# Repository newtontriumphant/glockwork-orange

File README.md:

# _Glockwork Orange_, by zsharpminor

A "Clockwork Orange" is defined as a human being who has had their free will and moral agency mechanically stripped away, turning them into a predictable, unthinking mechanism controlled by outside forces like the state. The human's natural "juicy" state is manifest in the orange, whereas the clockwork represents the unnaturality and cold predictability of the system.

Anyways, enough 1984; hiya! I'm Udo, better known as @zsharpminor or gh/newtontriumphant, and I have a thing for self-playing instruments. In late 2025, I won Honorable Mention at Hack Club x AMD's _Prototype_ flagship hackathon with [FiddleStein](https://github.com/newtontriumphant/Hackclub_Prototype_Fiddlestein), a fully self-playing violin that utilized a SO-101 robot arm and a 10k-step neural network to imitate a real human arm playing violin. FiddleStein was a great concept, but it sounded _mildly bad_, to be polite. Ever since early 2026, I wanted to create another self-playing instrument that would fit in well with FiddleStein, and Glockwork Orange was the logical next step.

## About Glockwork Orange

Glockwork Orange is a fully self-playing chromatic Glockenspiel that relies on solenoids to play ANY midi file payload by adjusting the instrumentation to fit into two voices!

> Sidenote: in the musical percussion and orchestra community, "glock" is used to abbreviate "glockenspiel" and is in no way related to the firearm brand created by Gaston Glock.

Glockwork Orange was designed for [Hack Club Outpost](https://outpost.hackclub.com/) as an X-Tier project, and is [on the list of X-Tier approved projects](https://docs.google.com/document/d/1faTrnYnGDMR5YSOkvKIAk_NsVOftPFZkB7XtJXA-l8c/edit?tab=t.0) sent out by [@CAN](https://hackclub.slack.com/archives/C0B519PGU22/p1781193322652829?thread_ts=1781016229.290339&cid=C0B519PGU22).

Anyways, enough yapping. A picture plays more than a thousand notes, or however the saying goes. Feast your eyes on the final assembled mockup of Glockwork Orange below.

---

At this point, you're probably asking: **how does this lie-detector-looking-thing work?!&**

Well, it's quite simple.

1. The Arduino sends a logic signal to the PCB being striked.
2. The power supply pushes out 15V and routes it into the PCB chain.
3. The respective PCB converts that signal to the current and voltage required to operate the solenoids.
4. The MOSFET briefly powers the solenoid and, by extension, the LED.
5. The solenoid strikes the key and immediately retracts.
6. Repeat (but don't rinse. handwashing is very bad when it comes to PCBs)!

## The PCB

Glockwork Orange's PCB uses a clever arrangement of transistors, resistors, capacitors, and a MOSFET to power the white JST connectors and their respective fading red LEDs each time the individual MOSFET is triggered.

Oh? What do I hear? You're wondering how this monstrosity was wired? If you have any experience doing ground planes on PCBs, I'd recommend you avert your eyes.

I've also included an image of the PCB's schematic:

The way this schematic works is by dividing the three inputs from the Arduino into segments, which each result in one JST connector and LED being powered at one time.

## The CAD

The way this project works is that it relies on the individual components being screwed down into a plywood project panel with M2 screws. That's why there's M2 screws on EVERY SINGLE COMPONENT in my CAD folder. 

For more information, including images and in-progress screenshots of every single CAD part, refer to [JOURNAL.md](JOURNAL.md). I won't entirely leave you hanging, though. Here's a side-view:

The blue parts are the solenoid holders I designed, and they slot onto the red holder bar that I also designed. The grey parts inside the blue holders refer to the actual solenoids.

## Wiring Diagram

Please excuse ~~my dear aunt sally~~ the sloppy wiring, this is only supposed to be *representative* of the final wiring!

```
+15V --> Red
Shared GND --> Black
Solenoid +/- --> Green
Arduino Signal --> Blue
```

## Firmware

The Glockwork Orange firmware consists of two files: `glockwork_orange.ino`, which runs on the Arduino Mega 2560 and maps all 25 chromatic keys (G2–A4, MIDI 43–69) to digital pins 22–46 driving the IRLZ44N MOSFET gate lines, and `glockwork_host.py`, a Python/Tkinter desktop GUI that parses any MIDI file, re-voices it into two chromatic voices within the glockenspiel's range via octave-shifting, and streams precisely-timed strike commands over USB serial at 115200 baud. The Arduino firmware uses a non-blocking 32-slot ring buffer to schedule and execute 35ms solenoid pulses without any delay() calls, which means the timing is, dare I say so myself, quite accurate across simultaneous voices. The host communicates via a simple ASCII protocol (S to start, N{ms},{note} to schedule a strike, X to stop), making it straightforward to extend or replace the Python frontend with any serial-capable environment.

## The Why And The How

Why did I make Glockwork Orange? Well, this one's pretty simple. I always wanted to make a successor to FiddleStein, one that could permanently work and be mounted in place with actual PCBs rather than precarious wiring and hot glue. (Also, using it to get into Outpost was a pretty fun motivation!)

How did I make Glockwork Orange? The entire process is in [JOURNAL.md](JOURNAL.md). Go read it. No, seriously. A lot of research went into this project, and it's a culmination of thoughts and solenoids. TL;DR, the answer is Patience (and a lack thereof).

## Directory

```
.
├── Assets/ <-- Some of the most important images found in this README
├── CAD/ <-- All CAD source files, as well as a .f3z Archive
├── Firmware/ <-- Simple firmware for the Arduino
├── PCB/ <-- KiCad source files of the PCB, .STEP export of PCB
├── Production/ <-- Gerber files and zipped Gerber files
├── BOM.csv <-- All components required to build this monstrosity
├── JOURNAL.md <-- Detailed explanation and tracking of hours
└── README.md <-- This file!
```

## Mini BOM

**NOTE**: The full BOM is located at [BOM.csv](BOM.csv). PLEASE READ IT. THIS IS ONLY A BREAKDOWN.

**CART SCREENSHOTS** can be found in the [Assets/Cart-Screenshots](Assets/Cart-Screenshots/Digikey_Cart_Final.png) folder. PII has been redacted. If the originals are required, DM @zsharpminor on the Hack Club Slack.

| Item | Total | Link |
| :--- | ---: | :---: |
| DigiKey Components | $480.00 | [↗](BOM.csv) |
| Amazon Components | $122.00 | [↗](BOM.csv) |
| Plywood from THD | $15.00 | [↗](BOM.csv) |
| JLCPCB PCB x 10 | $15.00 | [↗](BOM.csv) |
| Arduino and PSU | **OWNED** | - |
| | **$632.00** | |

## Disclosure of AI Usage

No Artificial Intelligence was used in creating the PCB, Schematic, any of the CAD, or README / JOURNAL.

AI was solely used to automate placing links into the BOM (~10% of BOM tracked hours), and for minor assistance with the code (see bottom of [JOURNAL.md](JOURNAL.md) for additional information), and for creating a custom footprint for an obsolete capacitor.

## License

GNU General Public License (GPL)

---

Thanks for reading down all this way! If you have any questions, please reach out to me via the Hack Club Slack @zsharpminor

Made with ♡ by zsharpminor

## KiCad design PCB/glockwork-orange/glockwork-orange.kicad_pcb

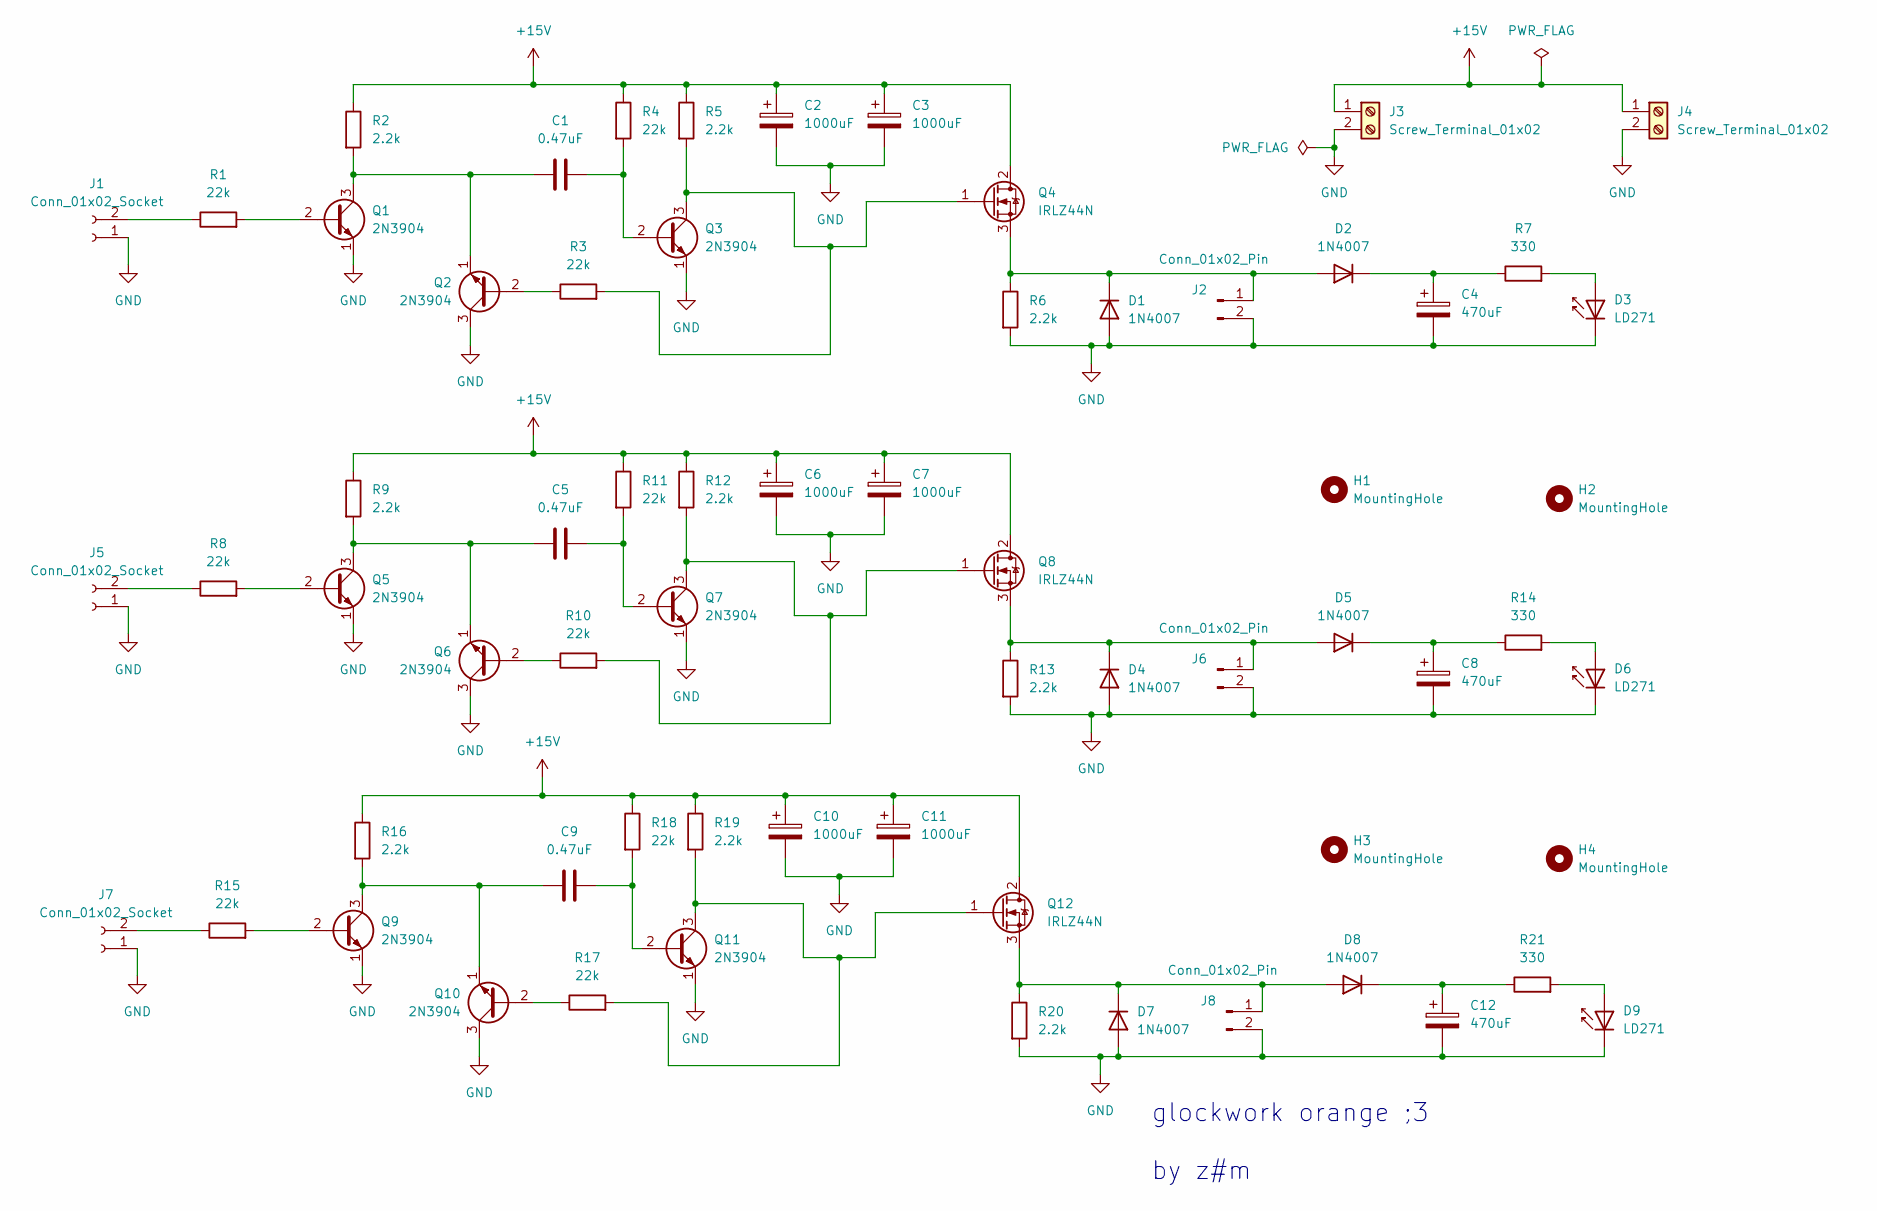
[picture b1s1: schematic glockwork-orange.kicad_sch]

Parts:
C1, C5, C9: 0.47uF; CAPRR750W80L1750T580H1400
C2, C3, C6, C7, C10, C11: 1000uF; CP_Radial_D12.5mm_P5.00mm
C4, C8, C12: 470uF; CP_Radial_D8.0mm_P3.50mm
D1, D2, D4, D5, D7, D8: 1N4007; D_DO-41_SOD81_P10.16mm_Horizontal
D3: LD271; LED_D5.0mm
D6, D9: LD271; LED_D5.0mm_IRGrey
H1, H2, H3, H4: MountingHole; MountingHole_2.2mm_M2
J1, J5, J7: Conn_01x02_Socket; PinSocket_1x02_P2.54mm_Vertical
J2, J6, J8: Conn_01x02_Pin; JST_PH_B2B-PH-K_1x02_P2.00mm_Vertical
J3, J4: Screw_Terminal_01x02; TerminalBlock_Phoenix_MKDS-1,5-2-5.08_1x02_P5.08mm_Horizont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
Q1, Q2, Q3, Q5, Q6, Q7, Q9, Q10, Q11: 2N3904; TO-92_Inline
Q4, Q8, Q12: IRLZ44N; TO-220-3_Vertical
R1, R3, R4, R8, R10, R11, R15, R17, R18: 22k; R_Axial_DIN0207_L6.3mm_D2.5mm_P10.16mm_Horizontal
R2, R5, R6, R9, R12, R13, R16, R19, R20: 2.2k; R_Axial_DIN0309_L9.0mm_D3.2mm_P12.70mm_Horizontal
R7, R14, R21: 330; R_Axial_DIN0207_L6.3mm_D2.5mm_P7.62mm_Horizontal

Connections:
+15V: C2.1, C3.1, C6.1, C7.1, C10.1, C11.1, J3.1, J4.1, Q4.2 (D), Q8.2 (D), Q12.2 (D), R2.1, R4.1, R5.1, R9.1, R11.1, R12.1, R16.1, R18.1, R19.1
GND: C2.2, C3.2, C4.2, C6.2, C7.2, C8.2, C10.2, C11.2, C12.2, D1.2 (A), D3.1 (K), D4.2 (A), D6.1 (K), D7.2 (A), D9.1 (K), J1.1, J2.2, J3.2, J4.2, J5.1, J6.2, J7.1, J8.2, Q1.1 (E), Q2.3 (C), Q3.1 (E), Q5.1 (E), Q6.3 (C), Q7.1 (E), Q9.1 (E), Q10.3 (C), Q11.1 (E), R6.2, R13.2, R20.2
unnamed: D1.1 (K), D2.2 (A), J2.1, Q4.3 (S), R6.1
unnamed: C4.1, D2.1 (K), R7.1
unnamed: D3.2 (A), R7.2
unnamed: D4.1 (K), D5.2 (A), J6.1, Q8.3 (S), R13.1
unnamed: C8.1, D5.1 (K), R14.1
unnamed: D6.2 (A), R14.2
unnamed: D7.1 (K), D8.2 (A), J8.1, Q12.3 (S), R20.1
unnamed: C12.1, D8.1 (K), R21.1
unnamed: D9.2 (A), R21.2
unnamed: J1.2, R1.1
unnamed: J5.2, R8.1
unnamed: J7.2, R15.1
unnamed: Q1.2 (B), R1.2
unnamed: C1.1, Q1.3 (C), Q2.1 (E), R2.2
unnamed: Q2.2 (B), R3.1
unnamed: C1.2, Q3.2 (B), R4.2
unnamed: Q3.3 (C), Q4.1 (G), R3.2, R5.2
unnamed: Q5.2 (B), R8.2
unnamed: C5.1, Q5.3 (C), Q6.1 (E), R9.2
unnamed: Q6.2 (B), R10.1
unnamed: C5.2, Q7.2 (B), R11.2
unnamed: Q7.3 (C), Q8.1 (G), R10.2, R12.2
unnamed: Q9.2 (B), R15.2
unnamed: Q10.2 (B), R17.1
unnamed: C9.1, Q9.3 (C), Q10.1 (E), R16.2
unnamed: C9.2, Q11.2 (B), R18.2
unnamed: Q11.3 (C), Q12.1 (G), R17.2, R19.2

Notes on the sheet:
glockwork orange ;3 by z#m

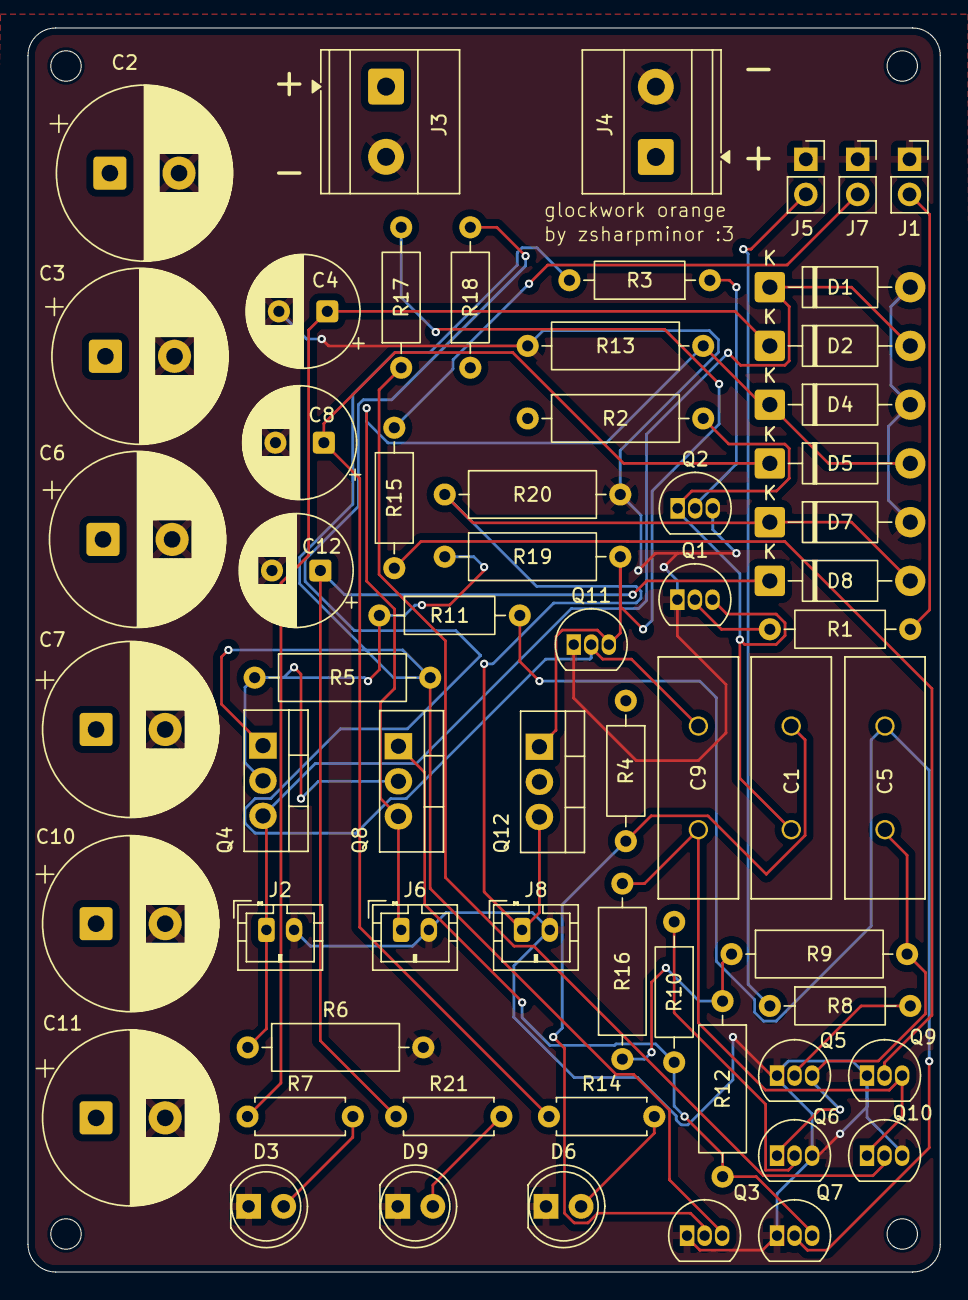
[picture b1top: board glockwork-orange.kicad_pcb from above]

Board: 2 copper layers, 66.0 x 90.0 mm, 66 parts (0 on the bottom side), 29 nets.

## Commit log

2026-06-13 Initial README update.
2026-06-13 Journal Day One
2026-06-17 Journal Day Two
2026-06-25 Journal Entries 3 & 4, Finished First Draft of PCB
2026-06-27 Journal Entry Five, Added PCB .step
2026-06-27 Final Design Journal Entry (6), Added All Reqd Files To Submit.
2026-06-28 Extremely Minor README Updates (Display Issues)
